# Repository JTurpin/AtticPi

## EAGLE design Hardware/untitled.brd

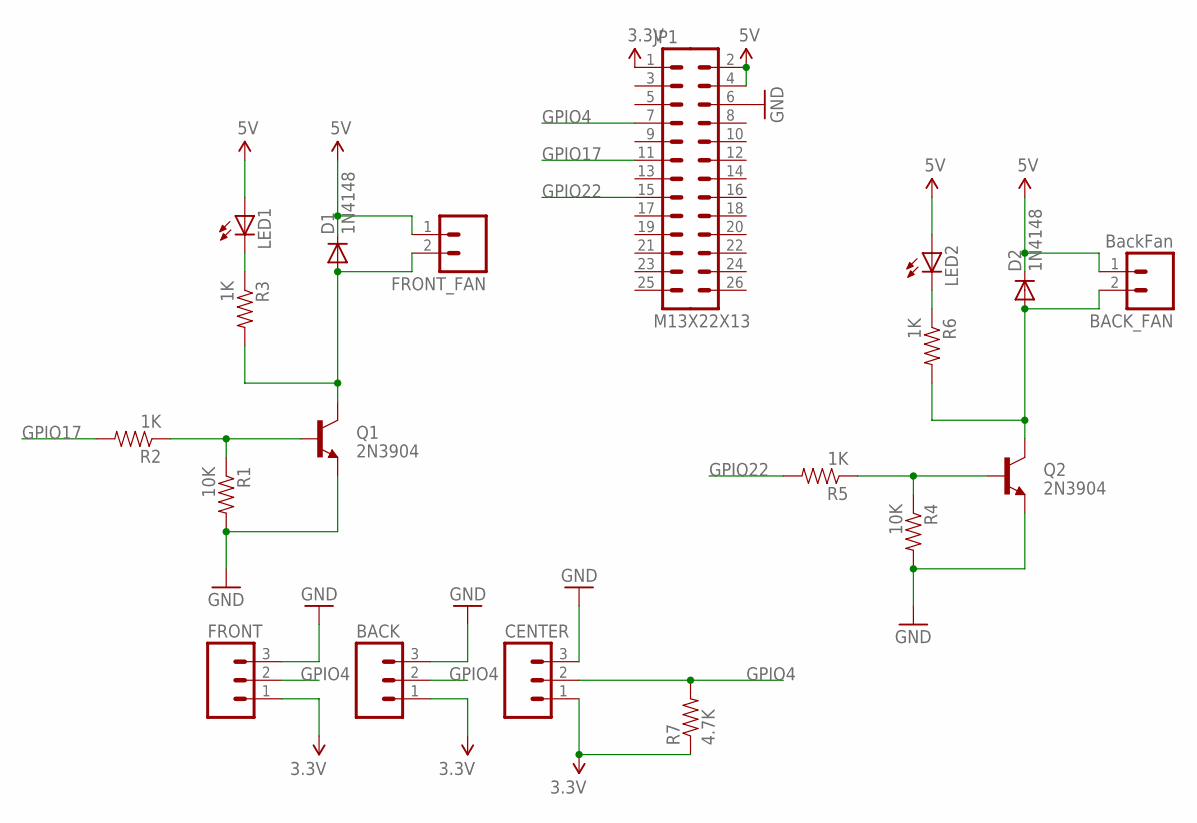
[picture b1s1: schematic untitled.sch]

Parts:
BACK: M03LOCK_LONGPADS; 1X03_LOCK_LONGPADS
BACK_FAN: BackFan; 1X02_LOCK_LONGPADS
CENTER: M03LOCK_LONGPADS; 1X03_LOCK_LONGPADS
D1, D2: 1N4148; DIODE-1N4148
FRONT: M03LOCK_LONGPADS; 1X03_LOCK_LONGPADS
FRONT_FAN: M02LOCK_LONGPADS; 1X02_LOCK_LONGPADS
JP1: M13X22X13; 2X13
LED1, LED2: LED5MM
Q1, Q2: 2N3904; TO-92
R1, R4: 10K; 0805
R2, R3, R5, R6: 1K; 0805
R7: 4.7K; 0805

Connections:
3.3V: BACK.1, CENTER.1, FRONT.1, JP1.1, R7.1
5V: BACK_FAN.1, D1.C, D2.C, FRONT_FAN.1, JP1.2, JP1.4, LED1.A, LED2.A
GND: BACK.3, CENTER.3, FRONT.3, JP1.6, Q1.1 (E), Q2.1 (E), R1.2, R4.2
GPIO4: BACK.2, CENTER.2, FRONT.2, JP1.7, R7.2
GPIO17: JP1.11, R2.2
GPIO22: JP1.15, R5.2
unnamed: LED1.K (C), R3.1
unnamed: Q1.2 (B), R1.1, R2.1
unnamed: D1.A, FRONT_FAN.2, Q1.3 (C), R3.2
unnamed: LED2.K (C), R6.1
unnamed: Q2.2 (B), R4.1, R5.1
unnamed: BACK_FAN.2, D2.A, Q2.3 (C), R6.2

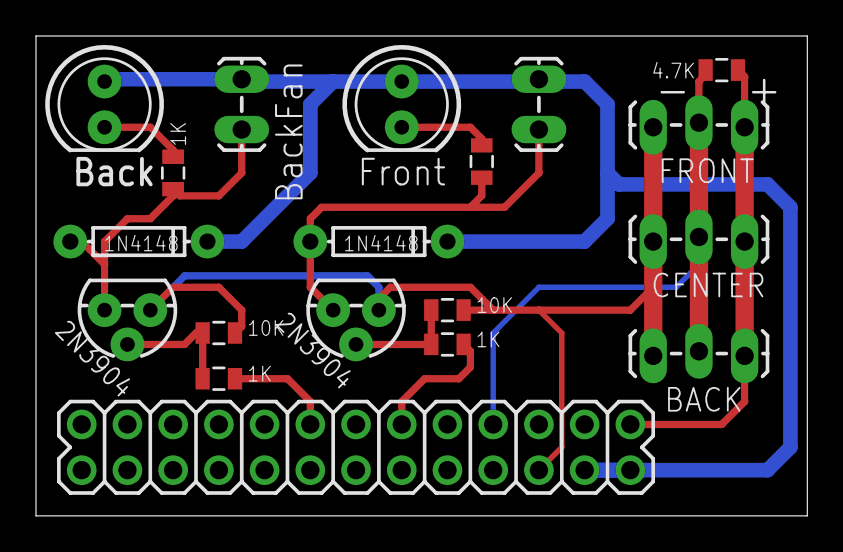
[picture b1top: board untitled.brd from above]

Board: 2 copper layers, 42.9 x 26.7 mm, 19 parts (0 on the bottom side), 12 nets.

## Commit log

2013-06-13 Old board cleanup
2013-06-13 Cleaned up files and board labels
2013-06-13 copied over all code currently in use
2013-06-13 fixed wrong file extension
2013-06-14 missing some equal signs.
2013-06-14 Added some logging and skipping sending redundant messages to the gpio
2013-06-22 Restyling the frontend.
2013-06-22 Add fan_on and fan_off scripts along with timestamp lockfiles.
2013-06-24 Fix call to date.
2013-06-24 Quite a bit of changing for the frontend.
2013-06-24 Switching fan pins to the correct ones.
2013-07-05 Bunch of changes including outside temprature.
2013-07-06 a few cleanups and bug fixes.
2013-07-06 uncomment the gpio commands

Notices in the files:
parts and their libraries:
SparkFun-Connectors: Licensing: CC v3.0 Share-Alike You are welcome to use this library for commercial purposes.
